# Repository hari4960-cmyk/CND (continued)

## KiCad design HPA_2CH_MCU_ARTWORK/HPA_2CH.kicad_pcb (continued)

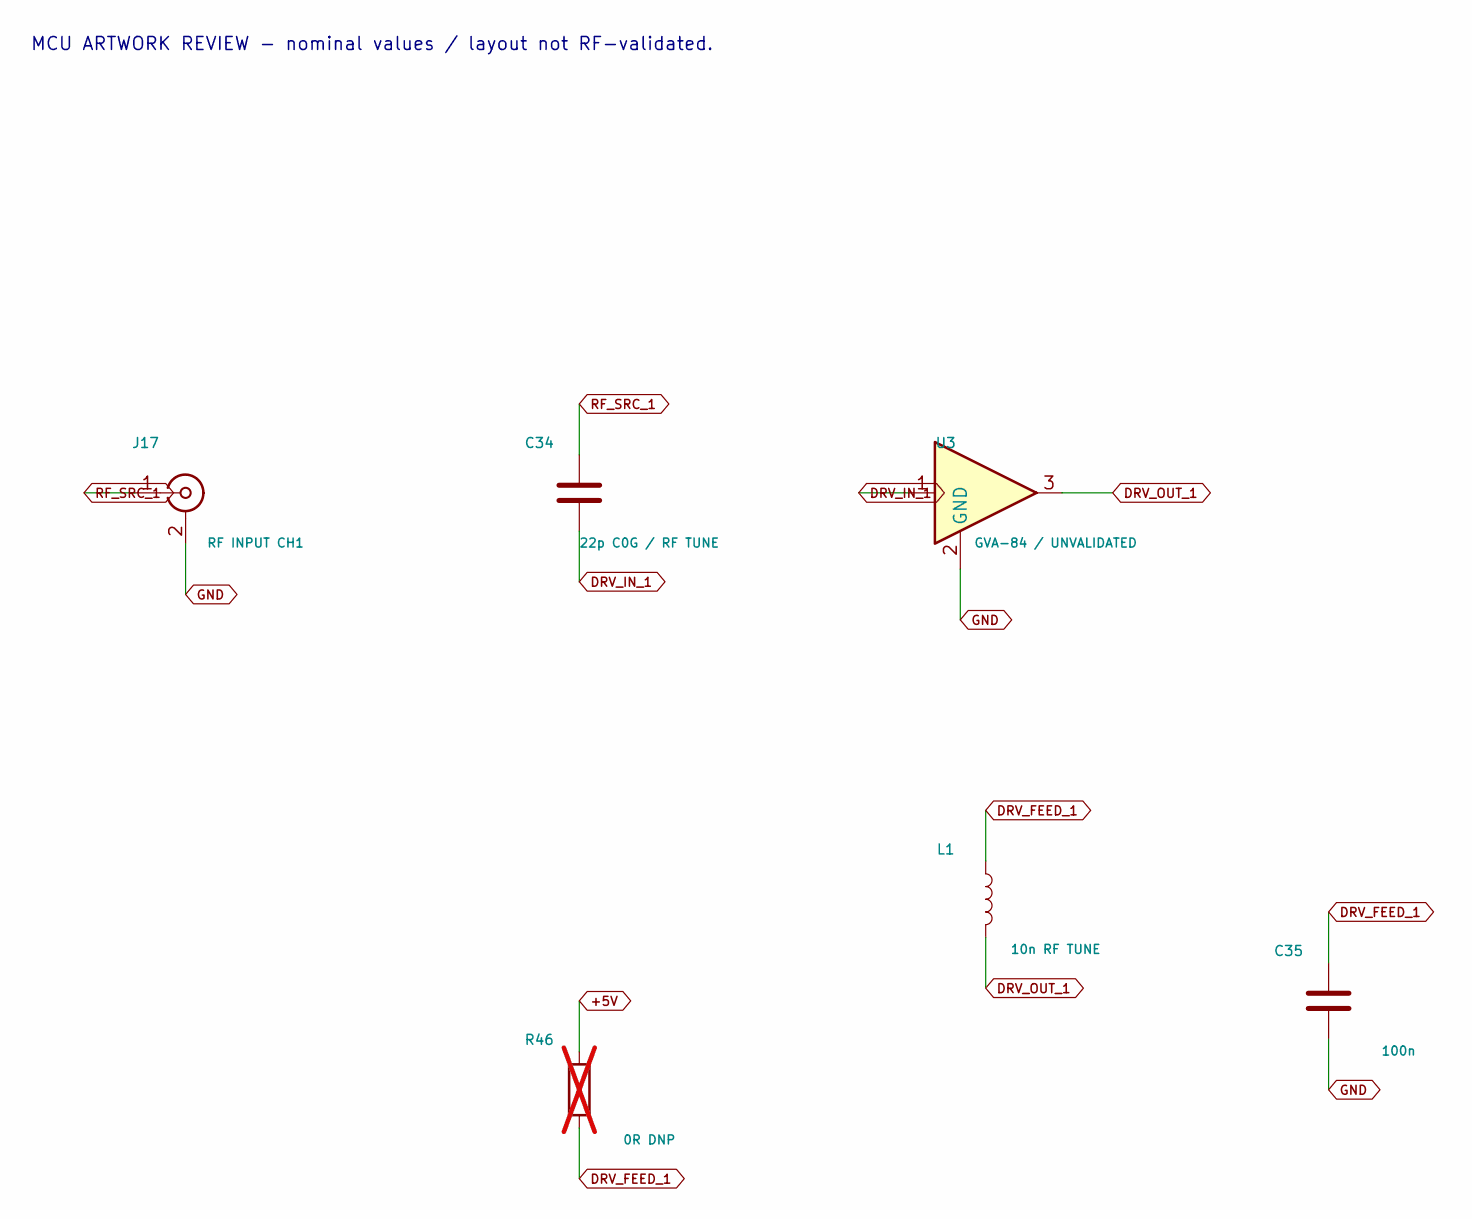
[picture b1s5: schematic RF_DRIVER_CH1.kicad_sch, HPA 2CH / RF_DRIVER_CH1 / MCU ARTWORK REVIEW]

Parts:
C34: 22p C0G / RF TUNE; C_0603_1608Metric
C35: 100n; C_0603_1608Metric
J17: RF INPUT CH1; SMA_Amphenol_132134_Vertical
L1: 10n RF TUNE; L_0805_2012Metric
R46: 0R DNP; R_0603_1608Metric; not fitted
U3: GVA-84 / UNVALIDATED; SOT-89-3

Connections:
+5V: R46.1; also elsewhere on the board
DRV_FEED_1: C35.1, L1.1, R46.2
DRV_IN_1: C34.2, U3.1
DRV_OUT_1: L1.2, U3.3; also elsewhere on the board
GND: C35.2, J17.2 (Ext), U3.2 (GND); also elsewhere on the board
RF_SRC_1: C34.1, J17.1 (In)

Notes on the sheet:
MCU ARTWORK REVIEW - nominal values / layout not RF-validated.

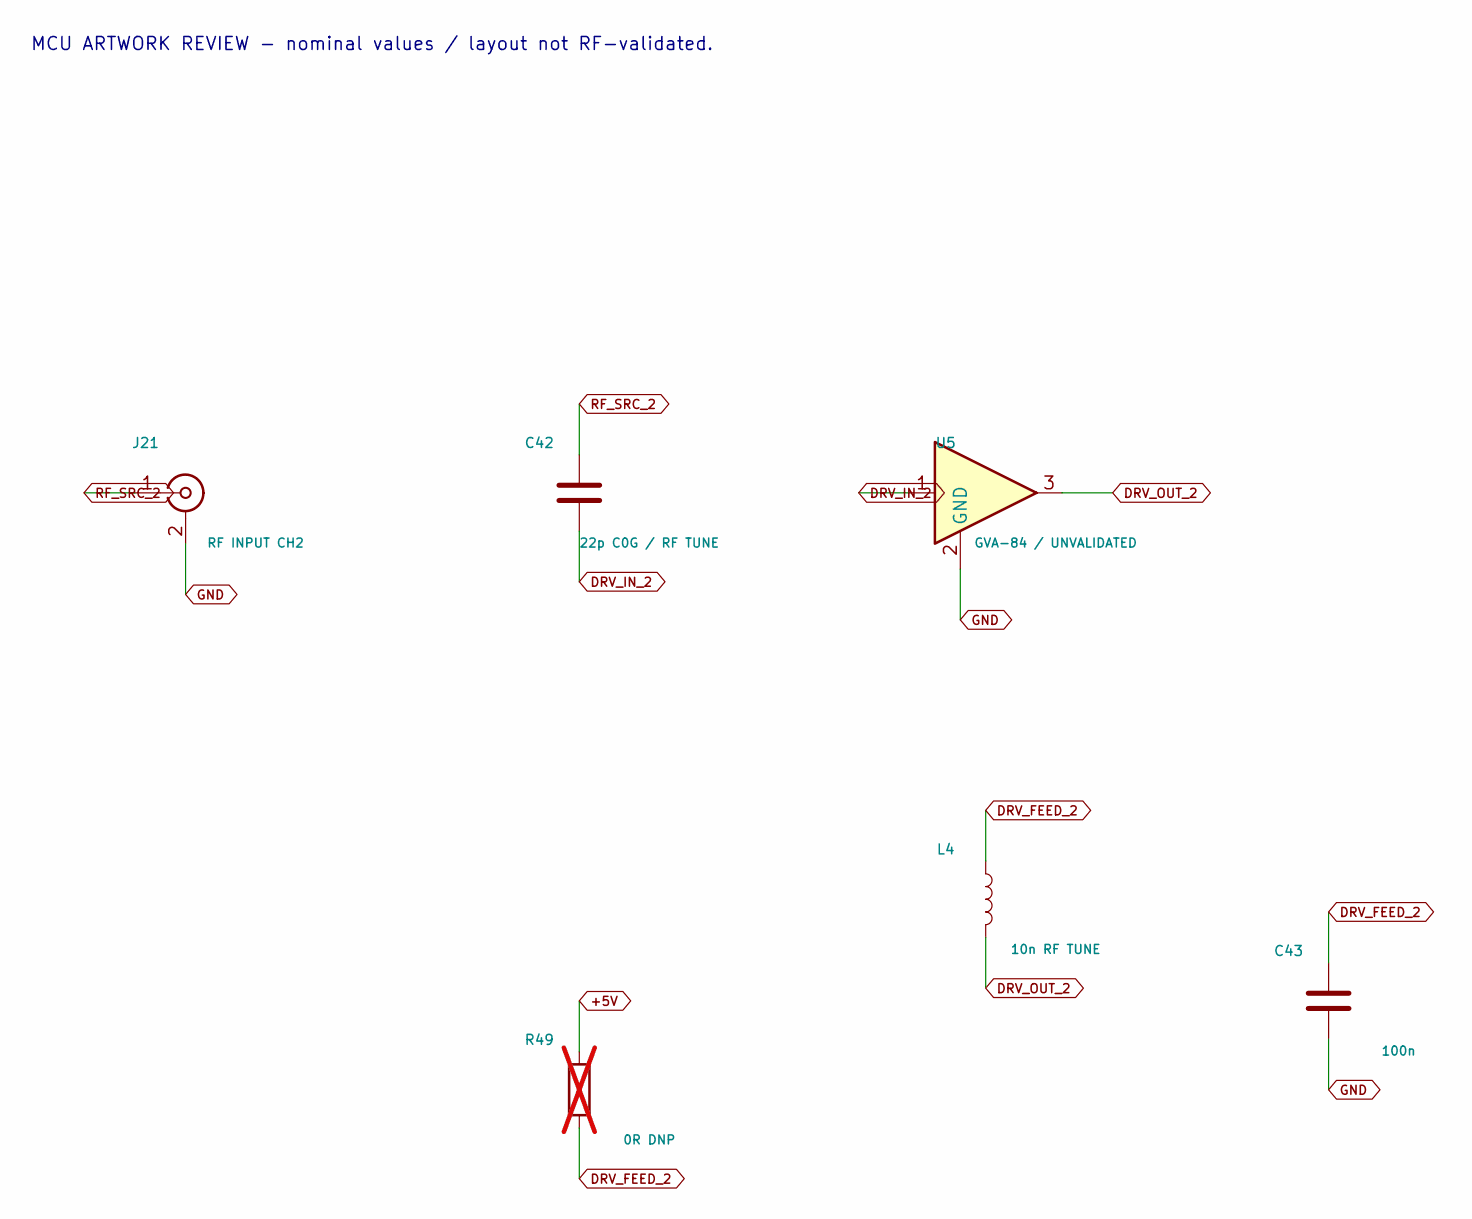
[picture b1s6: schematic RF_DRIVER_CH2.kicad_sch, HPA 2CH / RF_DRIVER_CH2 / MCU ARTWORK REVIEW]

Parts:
C42: 22p C0G / RF TUNE; C_0603_1608Metric
C43: 100n; C_0603_1608Metric
J21: RF INPUT CH2; SMA_Amphenol_132134_Vertical
L4: 10n RF TUNE; L_0805_2012Metric
R49: 0R DNP; R_0603_1608Metric; not fitted
U5: GVA-84 / UNVALIDATED; SOT-89-3

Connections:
+5V: R49.1; also elsewhere on the board
DRV_FEED_2: C43.1, L4.1, R49.2
DRV_IN_2: C42.2, U5.1
DRV_OUT_2: L4.2, U5.3; also elsewhere on the board
GND: C43.2, J21.2 (Ext), U5.2 (GND); also elsewhere on the board
RF_SRC_2: C42.1, J21.1 (In)

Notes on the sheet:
MCU ARTWORK REVIEW - nominal values / layout not RF-validated.

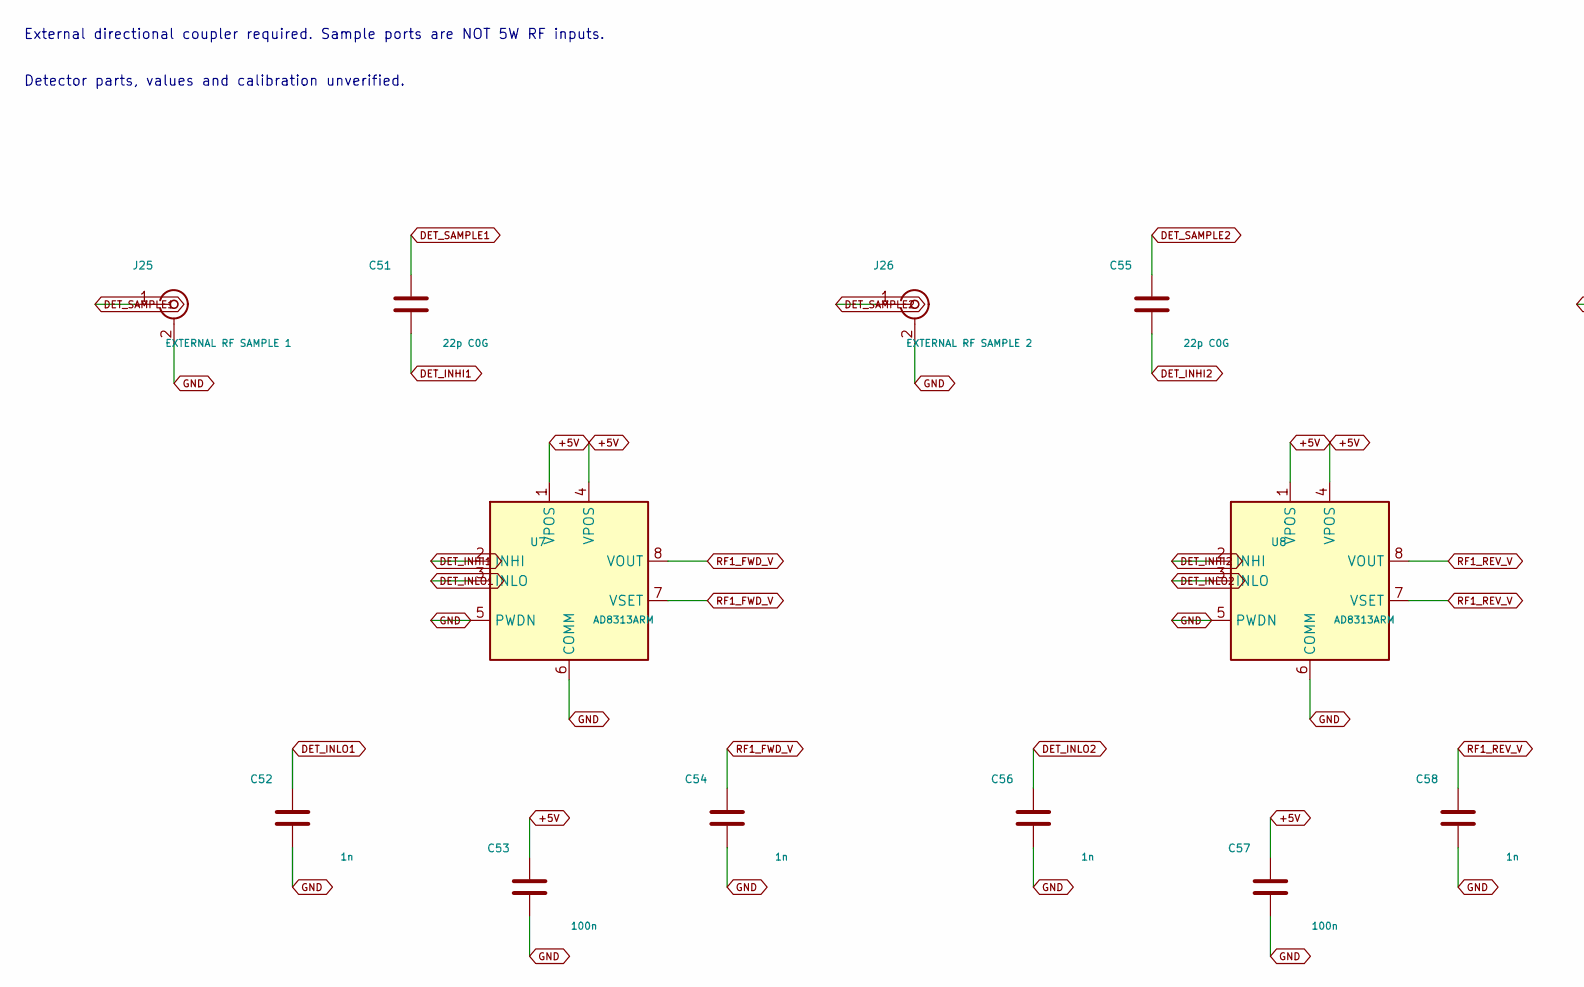
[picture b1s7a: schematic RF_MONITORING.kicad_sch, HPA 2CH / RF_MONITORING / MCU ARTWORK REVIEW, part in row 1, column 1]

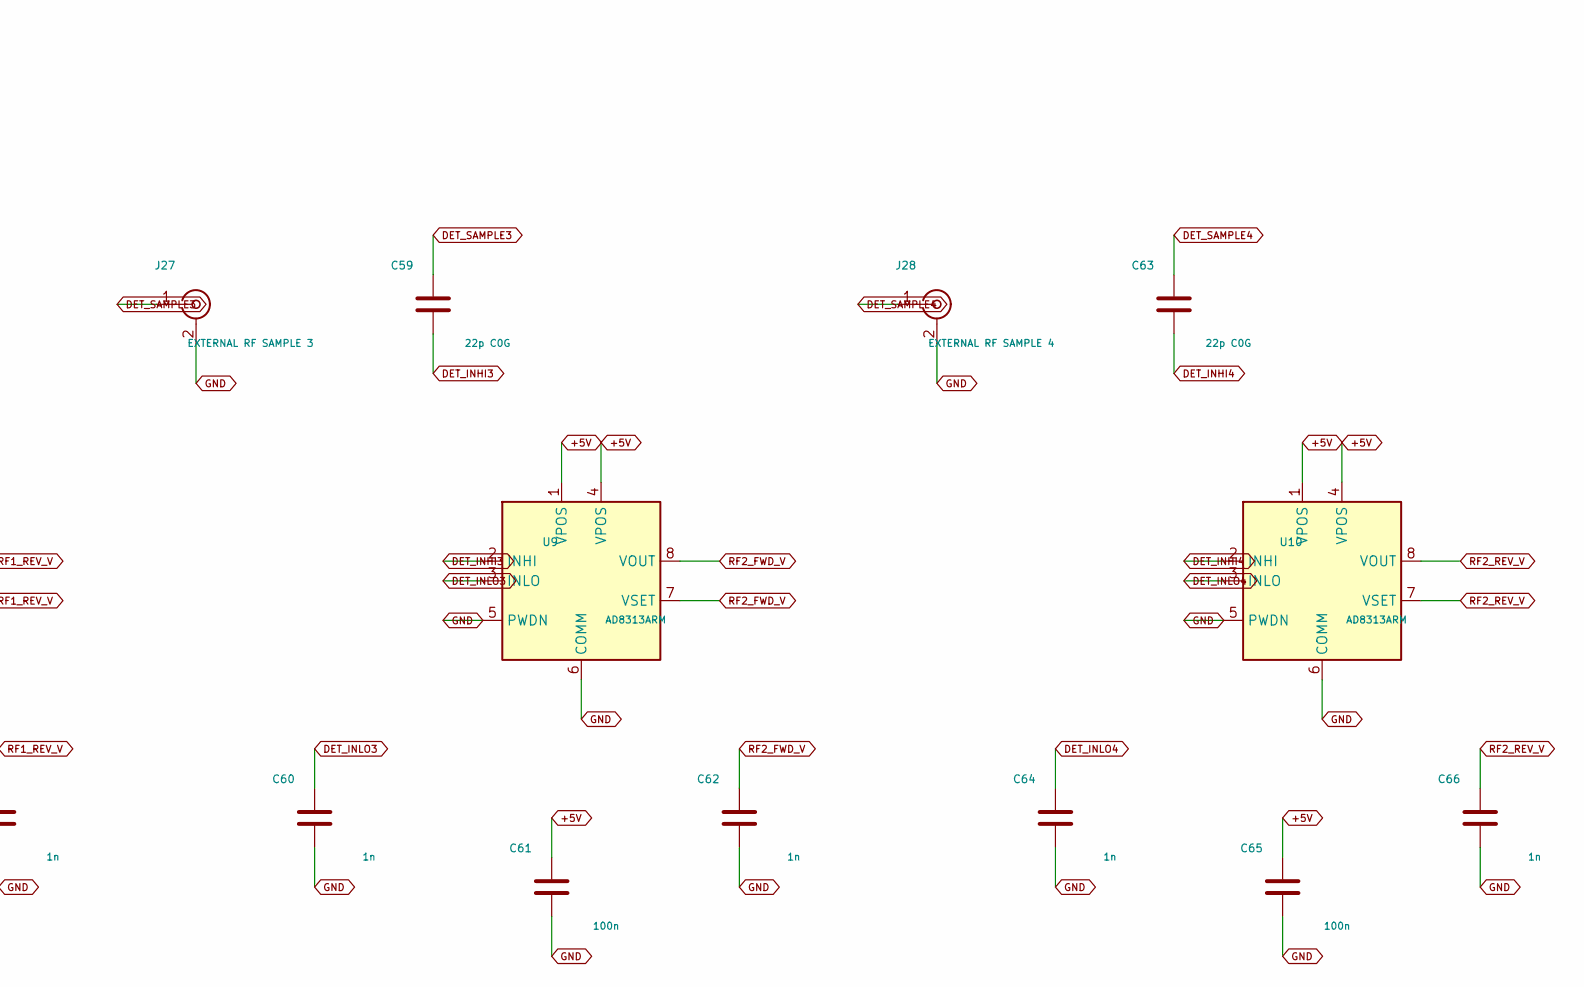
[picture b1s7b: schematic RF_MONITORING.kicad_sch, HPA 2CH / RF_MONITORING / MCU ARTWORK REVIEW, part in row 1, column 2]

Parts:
C51, C55, C59, C63: 22p C0G; C_0603_1608Metric
C52, C54, C56, C58, C60, C62, C64, C66: 1n; C_0603_1608Metric
C53, C57, C61, C65: 100n; C_0603_1608Metric
J25: EXTERNAL RF SAMPLE 1; SMA_Amphenol_132134_Vertical
J26: EXTERNAL RF SAMPLE 2; SMA_Amphenol_132134_Vertical
J27: EXTERNAL RF SAMPLE 3; SMA_Amphenol_132134_Vertical
J28: EXTERNAL RF SAMPLE 4; SMA_Amphenol_132134_Vertical
U7, U8, U9, U10: AD8313ARM; MSOP-8_3x3mm_P0.65mm

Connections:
+5V: C53.1, C57.1, C61.1, C65.1, U7.1 (VPOS), U7.4 (VPOS), U8.1 (VPOS), U8.4 (VPOS), U9.1 (VPOS), U9.4 (VPOS), U10.1 (VPOS), U10.4 (VPOS); also elsewhere on the board
DET_INHI1: C51.2, U7.2 (INHI)
DET_INHI2: C55.2, U8.2 (INHI)
DET_INHI3: C59.2, U9.2 (INHI)
DET_INHI4: C63.2, U10.2 (INHI)
DET_INLO1: C52.1, U7.3 (INLO)
DET_INLO2: C56.1, U8.3 (INLO)
DET_INLO3: C60.1, U9.3 (INLO)
DET_INLO4: C64.1, U10.3 (INLO)
DET_SAMPLE1: C51.1, J25.1 (In)
DET_SAMPLE2: C55.1, J26.1 (In)
DET_SAMPLE3: C59.1, J27.1 (In)
DET_SAMPLE4: C63.1, J28.1 (In)
GND: C52.2, C53.2, C54.2, C56.2, C57.2, C58.2, C60.2, C61.2, C62.2, C64.2, C65.2, C66.2, J25.2 (Ext), J26.2 (Ext), J27.2 (Ext), J28.2 (Ext), U7.5 (PWDN), U7.6 (COMM), U8.5 (PWDN), U8.6 (COMM), U9.5 (PWDN), U9.6 (COMM), U10.5 (PWDN), U10.6 (COMM); also elsewhere on the board
RF1_FWD_V: C54.1, U7.7 (VSET), U7.8 (VOUT); also elsewhere on the board
RF1_REV_V: C58.1, U8.7 (VSET), U8.8 (VOUT); also elsewhere on the board
RF2_FWD_V: C62.1, U9.7 (VSET), U9.8 (VOUT); also elsewhere on the board
RF2_REV_V: C66.1, U10.7 (VSET), U10.8 (VOUT); also elsewhere on the board

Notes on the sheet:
External directional coupler required. Sample ports are NOT 5W RF inputs.
Detector parts, values and calibration unverified.

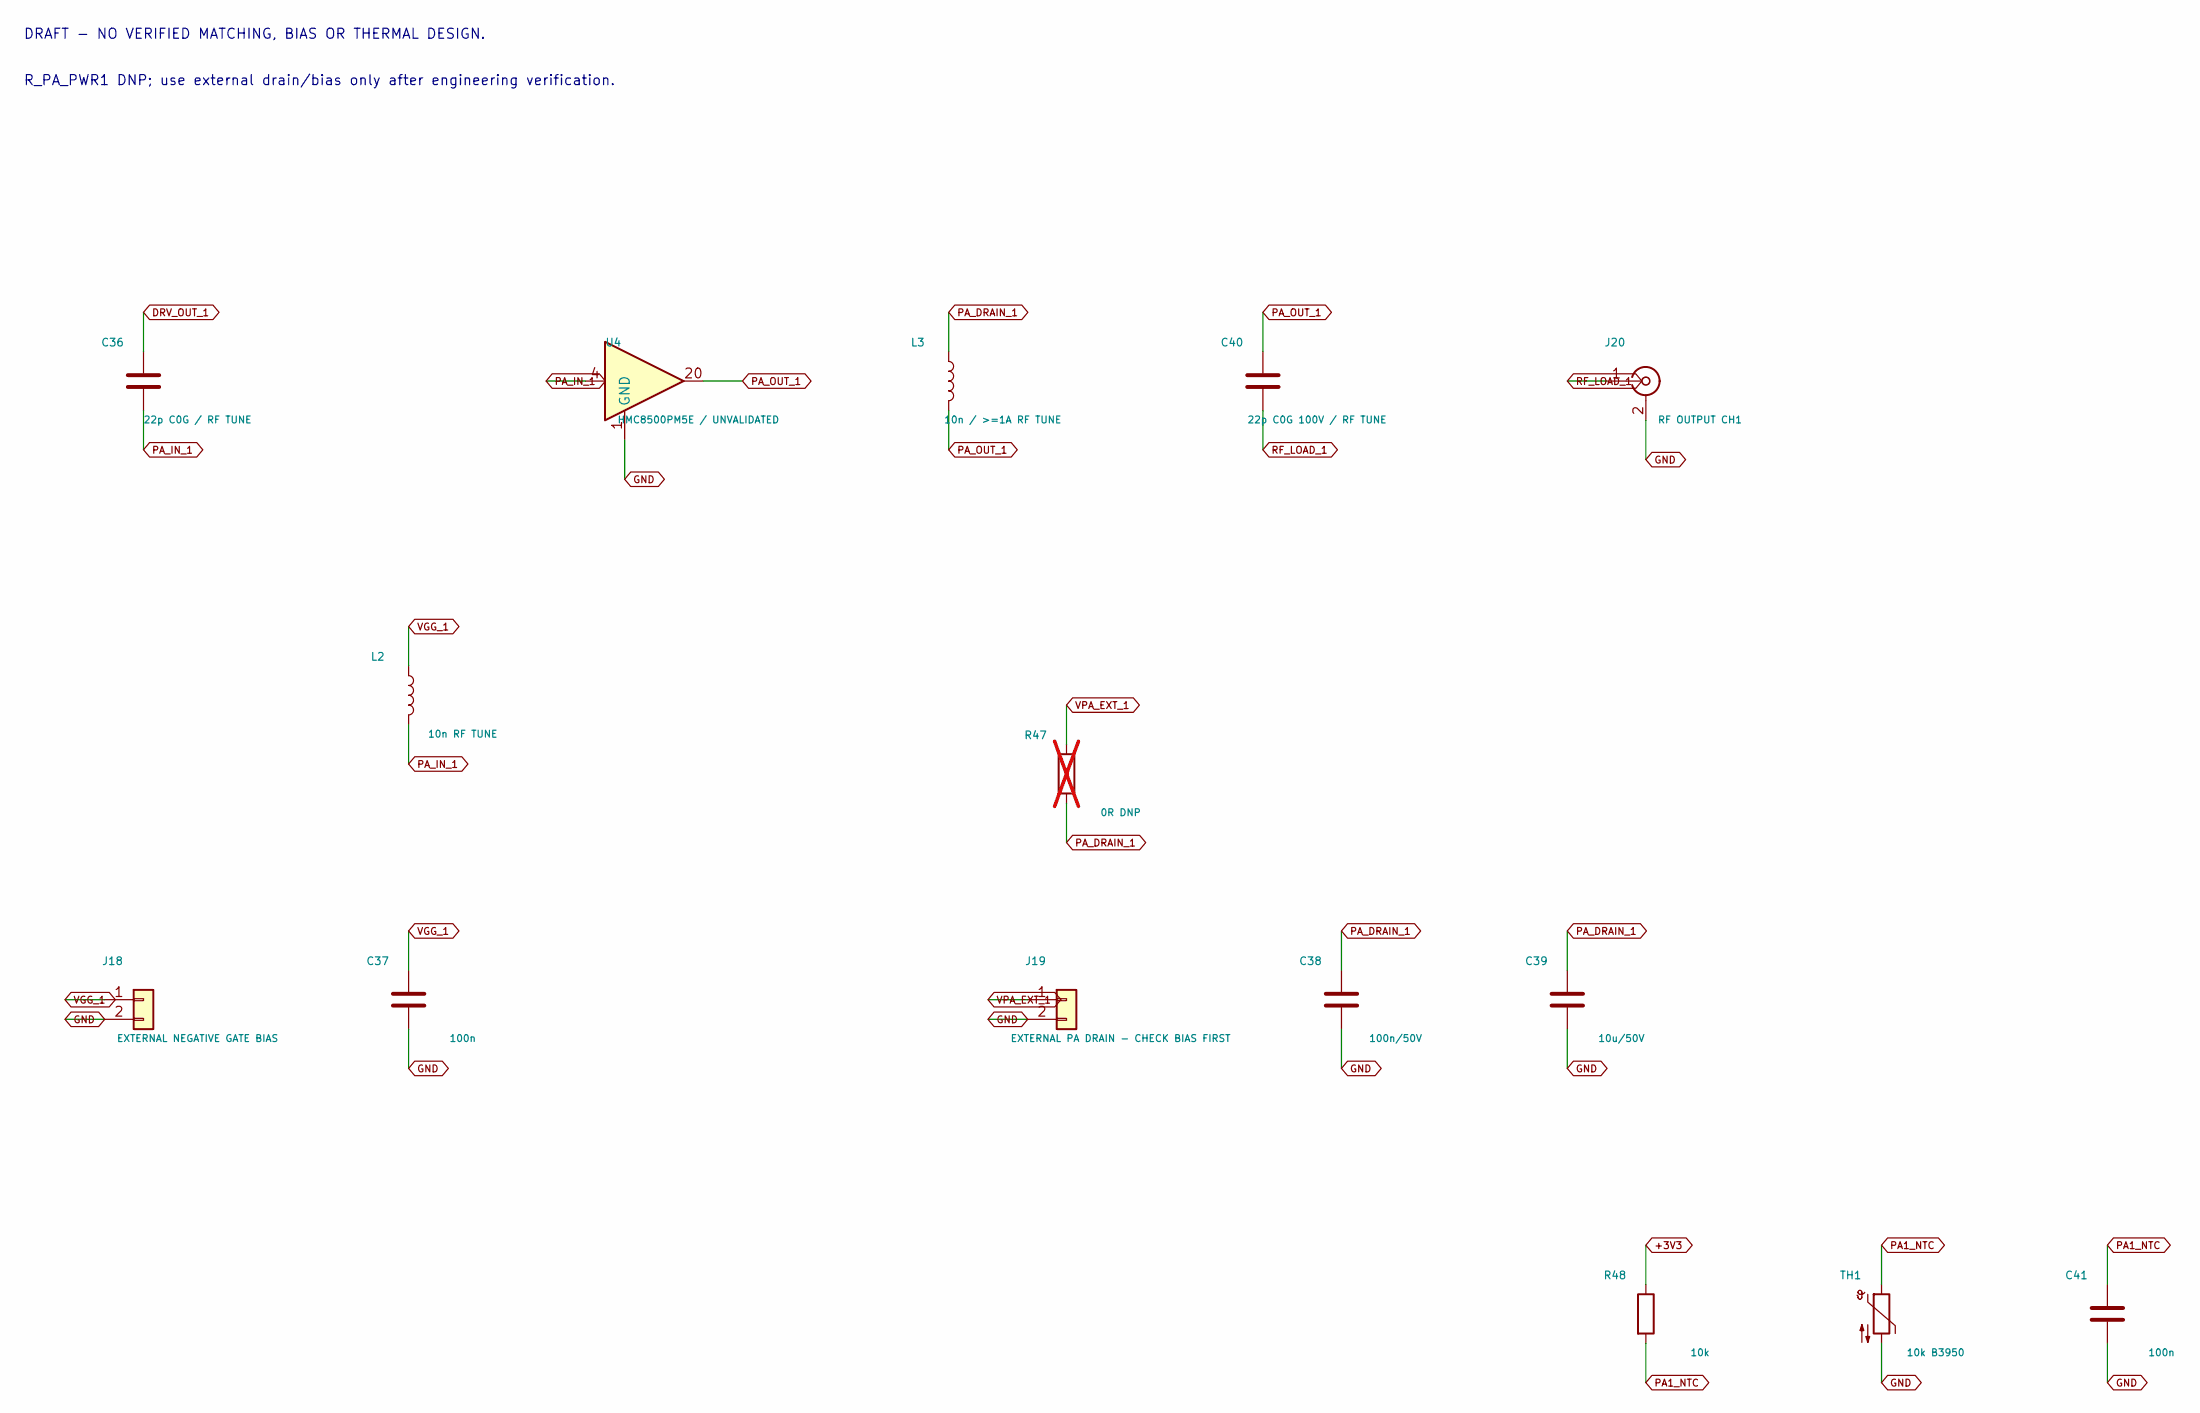
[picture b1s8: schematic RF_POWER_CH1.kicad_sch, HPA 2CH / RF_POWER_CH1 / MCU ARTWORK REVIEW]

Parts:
C36: 22p C0G / RF TUNE; C_0603_1608Metric
C37, C41: 100n; C_0603_1608Metric
C38: 100n/50V; C_0603_1608Metric
C39: 10u/50V; C_1210_3225Metric
C40: 22p C0G 100V / RF TUNE; C_0603_1608Metric
J18: EXTERNAL NEGATIVE GATE BIAS; PinHeader_1x02_P2.54mm_Vertical
J19: EXTERNAL PA DRAIN - CHECK BIAS FIRST; PinHeader_1x02_P2.54mm_Vertical
J20: RF OUTPUT CH1; SMA_Amphenol_132134_Vertical
L2: 10n RF TUNE; L_0805_2012Metric
L3: 10n / >=1A RF TUNE; L_0805_2012Metric
R47: 0R DNP; R_0603_1608Metric; not fitted
R48: 10k; R_0603_1608Metric
TH1: 10k B3950; R_0603_1608Metric
U4: HMC8500PM5E / UNVALIDATED; LFCSP-32-1EP_5x5mm_P0.5mm_EP3.1x3.1mm

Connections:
+3V3: R48.1; also elsewhere on the board
DRV_OUT_1: C36.1; also elsewhere on the board
GND: C37.2, C38.2, C39.2, C41.2, J18.2, J19.2, J20.2 (Ext), TH1.2, U4.1 (GND), U4.2 (GND), U4.3 (GND), U4.6 (GND), U4.7 (GND), U4.8 (GND), U4.9 (GND), U4.10 (GND), U4.11 (GND), U4.12 (GND), U4.13 (GND), U4.14 (GND), U4.15 (GND), U4.16 (GND), U4.17 (GND), U4.18 (GND), U4.19 (GND), U4.22 (GND), U4.23 (GND), U4.24 (GND), U4.25 (GND), U4.26 (GND), U4.27 (GND), U4.28 (GND), U4.29 (GND), U4.30 (GND), U4.31 (GND), U4.32 (GND), U4.33 (GND); also elsewhere on the board
PA1_NTC: C41.1, R48.2, TH1.1; also elsewhere on the board
PA_DRAIN_1: C38.1, C39.1, L3.1, R47.2
PA_IN_1: C36.2, L2.2, U4.4, U4.5
PA_OUT_1: C40.1, L3.2, U4.20, U4.21
RF_LOAD_1: C40.2, J20.1 (In)
VGG_1: C37.1, J18.1, L2.1
VPA_EXT_1: J19.1, R47.1; also elsewhere on the board

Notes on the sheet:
DRAFT - NO VERIFIED MATCHING, BIAS OR THERMAL DESIGN.
R_PA_PWR1 DNP; use external drain/bias only after engineering verification.

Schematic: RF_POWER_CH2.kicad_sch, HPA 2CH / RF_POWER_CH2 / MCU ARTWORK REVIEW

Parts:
C44: 22p C0G / RF TUNE; C_0603_1608Metric
C45, C49: 100n; C_0603_1608Metric
C46: 100n/50V; C_0603_1608Metric
C47: 10u/50V; C_1210_3225Metric
C48: 22p C0G 100V / RF TUNE; C_0603_1608Metric
J22: EXTERNAL NEGATIVE GATE BIAS; PinHeader_1x02_P2.54mm_Vertical
J23: EXTERNAL PA DRAIN - CHECK BIAS FIRST; PinHeader_1x02_P2.54mm_Vertical
J24: RF OUTPUT CH2; SMA_Amphenol_132134_Vertical
L5: 10n RF TUNE; L_0805_2012Metric
L6: 10n / >=1A RF TUNE; L_0805_2012Metric
R50: 0R DNP; R_0603_1608Metric; not fitted
R51: 10k; R_0603_1608Metric
TH2: 10k B3950; R_0603_1608Metric
U6: HMC8500PM5E / UNVALIDATED; LFCSP-32-1EP_5x5mm_P0.5mm_EP3.1x3.1mm

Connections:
+3V3: R51.1; also elsewhere on the board
DRV_OUT_2: C44.1; also elsewhere on the board
GND: C45.2, C46.2, C47.2, C49.2, J22.2, J23.2, J24.2 (Ext), TH2.2, U6.1 (GND), U6.2 (GND), U6.3 (GND), U6.6 (GND), U6.7 (GND), U6.8 (GND), U6.9 (GND), U6.10 (GND), U6.11 (GND), U6.12 (GND), U6.13 (GND), U6.14 (GND), U6.15 (GND), U6.16 (GND), U6.17 (GND), U6.18 (GND), U6.19 (GND), U6.22 (GND), U6.23 (GND), U6.24 (GND), U6.25 (GND), U6.26 (GND), U6.27 (GND), U6.28 (GND), U6.29 (GND), U6.30 (GND), U6.31 (GND), U6.32 (GND), U6.33 (GND); also elsewhere on the board
PA2_NTC: C49.1, R51.2, TH2.1; also elsewhere on the board
PA_DRAIN_2: C46.1, C47.1, L6.1, R50.2
PA_IN_2: C44.2, L5.2, U6.4, U6.5
PA_OUT_2: C48.1, L6.2, U6.20, U6.21
RF_LOAD_2: C48.2, J24.1 (In)
VGG_2: C45.1, J22.1, L5.1
VPA_EXT_2: J23.1, R50.1

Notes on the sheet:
DRAFT - NO VERIFIED MATCHING, BIAS OR THERMAL DESIGN.
R_PA_PWR2 DNP; use external drain/bias only after engineering verification.

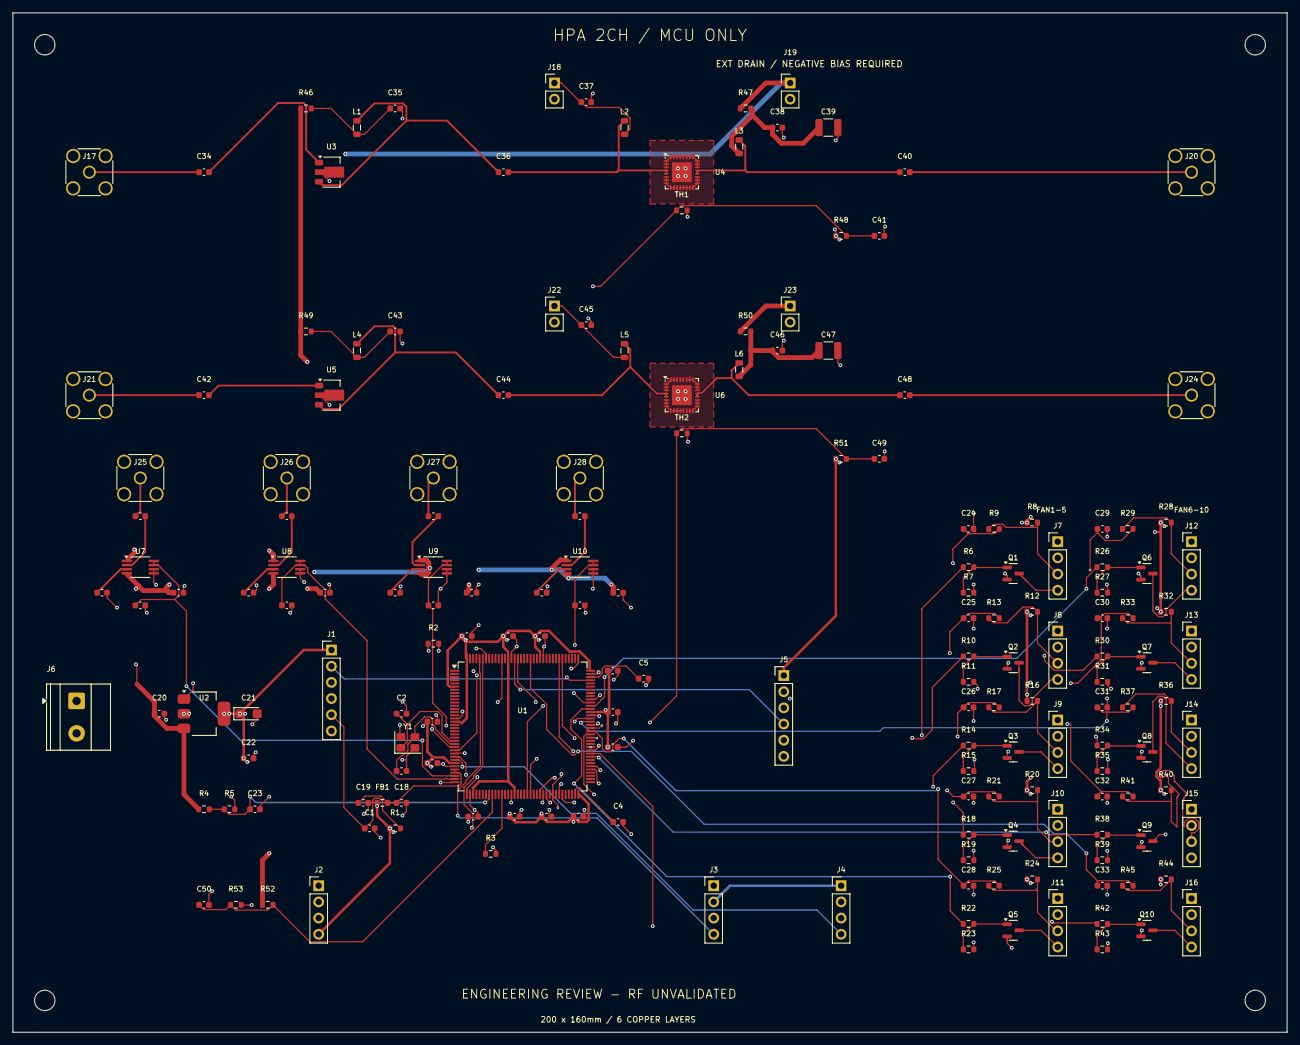
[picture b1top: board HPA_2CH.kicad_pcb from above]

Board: 6 copper layers, 200.0 x 160.0 mm, 181 parts (0 on the bottom side), 114 nets.

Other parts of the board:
H1, H2, H3, H4: MountingHole_3.2mm_M3

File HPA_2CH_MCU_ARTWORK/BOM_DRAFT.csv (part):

Reference,Function,Value,Footprint,DNP,Sheet
U1,U1,STM32F405ZGT6,Package_QFP:LQFP-144_20x20mm_P0.5mm,False,MAIN_CONTROLLER
J1,JSWD,SWD 3.3V + SWO,Connector_PinHeader_2.54mm:PinHeader_1x06_P2.54mm_Vertical,False,MAIN_CONTROLLER
J2,JUART,UART 3.3V,Connector_PinHeader_2.54mm:PinHeader_1x04_P2.54mm_Vertical,False,MAIN_CONTROLLER
J3,JI2C,I2C EXPANSION,Connector_PinHeader_2.54mm:PinHeader_1x04_P2.54mm_Vertical,False,MAIN_CONTROLLER
J4,JCURR,CURRENT 0..3.3V INPUTS,Connector_PinHeader_2.54mm:PinHeader_1x04_P2.54mm_Vertical,False,MAIN_CONTROLLER
J5,JRFCTRL,MCU RF CONTROL,Connector_PinHeader_2.54mm:PinHeader_1x06_P2.54mm_Vertical,False,MAIN_CONTROLLER
R1,R_RESET,10k,Resistor_SMD:R_0603_1608Metric,False,MAIN_CONTROLLER
C1,C_RESET,100n,Capacitor_SMD:C_0603_1608Metric,False,MAIN_CONTROLLER
R2,R_BOOT0,10k,Resistor_SMD:R_0603_1608Metric,False,MAIN_CONTROLLER
R3,R_BOOT1,10k,Resistor_SMD:R_0603_1608Metric,False,MAIN_CONTROLLER
Y1,Y1,8MHz / CL18pF,Crystal:Crystal_SMD_3225-4Pin_3.2x2.5mm,False,MAIN_CONTROLLER
C2,C_X1,33p C0G TUNE,Capacitor_SMD:C_0603_1608Metric,False,MAIN_CONTROLLER
C3,C_X2,33p C0G TUNE,Capacitor_SMD:C_0603_1608Metric,False,MAIN_CONTROLLER
C4,C_VCAP1,2.2u low ESR,Capacitor_SMD:C_0603_1608Metric,False,CORE_POWER
C5,C_VCAP2,2.2u low ESR,Capacitor_SMD:C_0603_1608Metric,False,CORE_POWER
C6,C_VDD17,100n,Capacitor_SMD:C_0603_1608Metric,False,CORE_POWER
C7,C_VDD30,100n,Capacitor_SMD:C_0603_1608Metric,False,CORE_POWER
C8,C_VDD39,100n,Capacitor_SMD:C_0603_1608Metric,False,CORE_POWER
C9,C_VDD52,100n,Capacitor_SMD:C_0603_1608Metric,False,CORE_POWER
C10,C_VDD62,100n,Capacitor_SMD:C_0603_1608Metric,False,CORE_POWER
C11,C_VDD72,100n,Capacitor_SMD:C_0603_1608Metric,False,CORE_POWER
C12,C_VDD84,100n,Capacitor_SMD:C_0603_1608Metric,False,CORE_POWER
C13,C_VDD95,100n,Capacitor_SMD:C_0603_1608Metric,False,CORE_POWER
C14,C_VDD108,100n,Capacitor_SMD:C_0603_1608Metric,False,CORE_POWER
C15,C_VDD121,100n,Capacitor_SMD:C_0603_1608Metric,False,CORE_POWER
C16,C_VDD131,100n,Capacitor_SMD:C_0603_1608Metric,False,CORE_POWER
C17,C_VDD144,100n,Capacitor_SMD:C_0603_1608Metric,False,CORE_POWER
FB1,FB1,600R@100MHz - VERIFY,Resistor_SMD:R_0603_1608Metric,False,CORE_POWER
C18,C_ADDA,100n,Capacitor_SMD:C_0603_1608Metric,False,CORE_POWER
C19,C_ADDB,1u,Capacitor_SMD:C_0603_1608Metric,False,CORE_POWER
J6,JPWR,+5V CONTROL/FANS,"TerminalBlock_Phoenix:TerminalBlock_Phoenix_MKDS-1,5-2-5.08_1x02_P5.08mm_Horizontal",False,CORE_POWER
U2,UREG,AMS1117-3.3,Package_TO_SOT_SMD:SOT-223-3_TabPin2,False,CORE_POWER
C20,C_IN,10u/10V,Capacitor_SMD:C_0603_1608Metric,False,CORE_POWER
C21,C_OUT,10u TANT / ESR VERIFY,Capacitor_Tantalum_SMD:CP_EIA-3216-18_Kemet-A,False,CORE_POWER
C22,C_BULK,4.7u,Capacitor_SMD:C_0603_1608Metric,False,CORE_POWER
R4,R_VIN_H,100k,Resistor_SMD:R_0603_1608Metric,False,CORE_POWER
R5,R_VIN_L,47k,Resistor_SMD:R_0603_1608Metric,False,CORE_POWER
C23,C_VINMON,100n,Capacitor_SMD:C_0603_1608Metric,False,CORE_POWER
J7,JF1,FAN1 5V 4WIRE,Connector_PinHeader_2.54mm:PinHeader_1x04_P2.54mm_Vertical,False,FAN_CONTROL
Q1,QF1,2N7002,Package_TO_SOT_SMD:SOT-23,False,FAN_CONTROL
R6,RG1,100,Resistor_SMD:R_0603_1608Metric,False,FAN_CONTROL
R7,RPD1,100k,Resistor_SMD:R_0603_1608Metric,False,FAN_CONTROL
R8,RTP1,10k,Resistor_SMD:R_0603_1608Metric,False,FAN_CONTROL
R9,RTS1,1k,Resistor_SMD:R_0603_1608Metric,False,FAN_CONTROL
C24,CT1,1n,Capacitor_SMD:C_0603_1608Metric,False,FAN_CONTROL
J8,JF2,FAN2 5V 4WIRE,Connector_PinHeader_2.54mm:PinHeader_1x04_P2.54mm_Vertical,False,FAN_CONTROL
Q2,QF2,2N7002,Package_TO_SOT_SMD:SOT-23,False,FAN_CONTROL
R10,RG2,100,Resistor_SMD:R_0603_1608Metric,False,FAN_CONTROL
R11,RPD2,100k,Resistor_SMD:R_0603_1608Metric,False,FAN_CONTROL
R12,RTP2,10k,Resistor_SMD:R_0603_1608Metric,False,FAN_CONTROL
R13,RTS2,1k,Resistor_SMD:R_0603_1608Metric,False,FAN_CONTROL
C25,CT2,1n,Capacitor_SMD:C_0603_1608Metric,False,FAN_CONTROL
J9,JF3,FAN3 5V 4WIRE,Connector_PinHeader_2.54mm:PinHeader_1x04_P2.54mm_Vertical,False,FAN_CONTROL
Q3,QF3,2N7002,Package_TO_SOT_SMD:SOT-23,False,FAN_CONTROL
R14,RG3,100,Resistor_SMD:R_0603_1608Metric,False,FAN_CONTROL
R15,RPD3,100k,Resistor_SMD:R_0603_1608Metric,False,FAN_CONTROL
R16,RTP3,10k,Resistor_SMD:R_0603_1608Metric,False,FAN_CONTROL
R17,RTS3,1k,Resistor_SMD:R_0603_1608Metric,False,FAN_CONTROL
C26,CT3,1n,Capacitor_SMD:C_0603_1608Metric,False,FAN_CONTROL
J10,JF4,FAN4 5V 4WIRE,Connector_PinHeader_2.54mm:PinHeader_1x04_P2.54mm_Vertical,False,FAN_CONTROL
Q4,QF4,2N7002,Package_TO_SOT_SMD:SOT-23,False,FAN_CONTROL
R18,RG4,100,Resistor_SMD:R_0603_1608Metric,False,FAN_CONTROL
R19,RPD4,100k,Resistor_SMD:R_0603_1608Metric,False,FAN_CONTROL
R20,RTP4,10k,Resistor_SMD:R_0603_1608Metric,False,FAN_CONTROL
R21,RTS4,1k,Resistor_SMD:R_0603_1608Metric,False,FAN_CONTROL
C27,CT4,1n,Capacitor_SMD:C_0603_1608Metric,False,FAN_CONTROL
J11,JF5,FAN5 5V 4WIRE,Connector_PinHeader_2.54mm:PinHeader_1x04_P2.54mm_Vertical,False,FAN_CONTROL
Q5,QF5,2N7002,Package_TO_SOT_SMD:SOT-23,False,FAN_CONTROL
R22,RG5,100,Resistor_SMD:R_0603_1608Metric,False,FAN_CONTROL
R23,RPD5,100k,Resistor_SMD:R_0603_1608Metric,False,FAN_CONTROL
R24,RTP5,10k,Resistor_SMD:R_0603_1608Metric,False,FAN_CONTROL
R25,RTS5,1k,Resistor_SMD:R_0603_1608Metric,False,FAN_CONTROL
C28,CT5,1n,Capacitor_SMD:C_0603_1608Metric,False,FAN_CONTROL
J12,JF6,FAN6 5V 4WIRE,Connector_PinHeader_2.54mm:PinHeader_1x04_P2.54mm_Vertical,False,FAN_CONTROL
Q6,QF6,2N7002,Package_TO_SOT_SMD:SOT-23,False,FAN_CONTROL
R26,RG6,100,Resistor_SMD:R_0603_1608Metric,False,FAN_CONTROL
R27,RPD6,100k,Resistor_SMD:R_0603_1608Metric,False,FAN_CONTROL
R28,RTP6,10k,Resistor_SMD:R_0603_1608Metric,False,FAN_CONTROL
R29,RTS6,1k,Resistor_SMD:R_0603_1608Metric,False,FAN_CONTROL
C29,CT6,1n,Capacitor_SMD:C_0603_1608Metric,False,FAN_CONTROL
J13,JF7,FAN7 5V 4WIRE,Connector_PinHeader_2.54mm:PinHeader_1x04_P2.54mm_Vertical,False,FAN_CONTROL
Q7,QF7,2N7002,Package_TO_SOT_SMD:SOT-23,False,FAN_CONTROL
R30,RG7,100,Resistor_SMD:R_0603_1608Metric,False,FAN_CONTROL
R31,RPD7,100k,Resistor_SMD:R_0603_1608Metric,False,FAN_CONTROL
R32,RTP7,10k,Resistor_SMD:R_0603_1608Metric,False,FAN_CONTROL
R33,RTS7,1k,Resistor_SMD:R_0603_1608Metric,False,FAN_CONTROL
C30,CT7,1n,Capacitor_SMD:C_0603_1608Metric,False,FAN_CONTROL
J14,JF8,FAN8 5V 4WIRE,Connector_PinHeader_2.54mm:PinHeader_1x04_P2.54mm_Vertical,False,FAN_CONTROL
Q8,QF8,2N7002,Package_TO_SOT_SMD:SOT-23,False,FAN_CONTROL
R34,RG8,100,Resistor_SMD:R_0603_1608Metric,False,FAN_CONTROL
R35,RPD8,100k,Resistor_SMD:R_0603_1608Metric,False,FAN_CONTROL
R36,RTP8,10k,Resistor_SMD:R_0603_1608Metric,False,FAN_CONTROL
R37,RTS8,1k,Resistor_SMD:R_0603_1608Metric,False,FAN_CONTROL
C31,CT8,1n,Capacitor_SMD:C_0603_1608Metric,False,FAN_CONTROL
J15,JF9,FAN9 5V 4WIRE,Connector_PinHeader_2.54mm:PinHeader_1x04_P2.54mm_Vertical,False,FAN_CONTROL
Q9,QF9,2N7002,Package_TO_SOT_SMD:SOT-23,False,FAN_CONTROL
R38,RG9,100,Resistor_SMD:R_0603_1608Metric,False,FAN_CONTROL
R39,RPD9,100k,Resistor_SMD:R_0603_1608Metric,False,FAN_CONTROL
R40,RTP9,10k,Resistor_SMD:R_0603_1608Metric,False,FAN_CONTROL
R41,RTS9,1k,Resistor_SMD:R_0603_1608Metric,False,FAN_CONTROL
C32,CT9,1n,Capacitor_SMD:C_0603_1608Metric,False,FAN_CONTROL
J16,JF10,FAN10 5V 4WIRE,Connector_PinHeader_2.54mm:PinHeader_1x04_P2.54mm_Vertical,False,FAN_CONTROL
Q10,QF10,2N7002,Package_TO_SOT_SMD:SOT-23,False,FAN_CONTROL
R42,RG10,100,Resistor_SMD:R_0603_1608Metric,False,FAN_CONTROL
R43,RPD10,100k,Resistor_SMD:R_0603_1608Metric,False,FAN_CONTROL
R44,RTP10,10k,Resistor_SMD:R_0603_1608Metric,False,FAN_CONTROL
R45,RTS10,1k,Resistor_SMD:R_0603_1608Metric,False,FAN_CONTROL
C33,CT10,1n,Capacitor_SMD:C_0603_1608Metric,False,FAN_CONTROL
J17,JRF_IN1,RF INPUT CH1,Connector_Coaxial:SMA_Amphenol_132134_Vertical,False,RF_DRIVER_CH1
C34,C_RFIN1,22p C0G / RF TUNE,Capacitor_SMD:C_0603_1608Metric,False,RF_DRIVER_CH1
U3,UDRV1,GVA-84 / UNVALIDATED,Package_TO_SOT_SMD:SOT-89-3,False,RF_DRIVER_CH1
L1,LDRV1,10n RF TUNE,Inductor_SMD:L_0805_2012Metric,False,RF_DRIVER_CH1
R46,R_DRV_PWR1,0R DNP,Resistor_SMD:R_0603_1608Metric,True,RF_DRIVER_CH1
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
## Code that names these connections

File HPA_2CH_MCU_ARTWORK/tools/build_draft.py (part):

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 if nm in ['VDDA','VREF+']:mp[num]='VDDA'
 if nm.startswith('VCAP'):mp[num]=nm
for n in ['NRST','BOOT0']:mp[pm[n]]=n
for n in ['PH0','PH1']:mp[pm[n]]='HSE_IN' if n=='PH0' else 'HSE_OUT'
mp[pm['PB2']]='BOOT1'
for i,g in enumerate(['PE9','PE11','PE13','PE14','PC6','PC7','PC8','PC9','PD12','PD13'],1):mp[pm[g]]=f'FAN_PWM_{i}'
for i in range(10):mp[pm[f'PG{i}']]=f'FAN_TACH_{i+1}'
for g,n in [('PG13','PA1_ENABLE_CMD'),('PG14','PA2_ENABLE_CMD'),('PD0','RF1_FAULT'),('PD1','RF2_FAULT'),('PD8','UART_TX'),('PD9','UART_RX'),('PB8','I2C_SCL'),('PB9','I2C_SDA'),('PA13','SWDIO'),('PA14','SWCLK'),('PB3','SWO')]:mp[pm[g]]=n
for i,n in enumerate(['RF1_FWD_V','RF1_REV_V','RF2_FWD_V','RF2_REV_V']):mp[pm[f'PA{i}']]=n
for i,n in enumerate(['PA1_NTC','PA2_NTC','PA1_I_MON','PA2_I_MON','VIN_MON','VPA_MON']):mp[pm[f'PC{i}']]=n
add('MAIN_CONTROLLER','U1','MCU_ST_STM32F4','STM32F405ZGTx','STM32F405ZGT6','Package_QFP:LQFP-144_20x20mm_P0.5mm',mp,(85,145),(80,112))
conn('MAIN_CONTROLLER','JSWD',6,'SWD 3.3V + SWO',{1:'+3V3',2:'SWDIO',3:'GND',4:'SWCLK',5:'NRST',6:'SWO'},(180,50),(52,92))
conn('MAIN_CONTROLLER','JUART',4,'UART 3.3V',{1:'GND',2:'UART_TX',3:'UART_RX',4:'+3V3'},(180,85),(48,137))
conn('MAIN_CONTROLLER','JI2C',4,'I2C EXPANSION',{1:'GND',2:'+3V3',3:'I2C_SCL',4:'I2C_SDA'},(180,120),(110,137))
conn('MAIN_CONTROLLER','JCURR',4,'CURRENT 0..3.3V INPUTS',{1:'+3V3',2:'GND',3:'PA1_I_MON',4:'PA2_I_MON'},(180,155),(130,137))
conn('MAIN_CONTROLLER','JRFCTRL',6,'MCU RF CONTROL',{1:'+3V3',2:'GND',3:'PA1_ENABLE_CMD',4:'PA2_ENABLE_CMD',5:'RF1_FAULT',6:'RF2_FAULT'},(180,210),(121,104))
resistor('MAIN_CONTROLLER','R_RESET','10k','+3V3','NRST',(260,45),(60,128));cap('MAIN_CONTROLLER','C_RESET','100n','NRST','GND',(280,45),(56,128))
resistor('MAIN_CONTROLLER','R_BOOT0','10k','BOOT0','GND',(260,80),(67,94));resistor('MAIN_CONTROLLER','R_BOOT1','10k','BOOT1','GND',(280,80),(75,132))
add('MAIN_CONTROLLER','Y1','Device','Crystal_GND24','8MHz / CL18pF','Crystal:Crystal_SMD_3225-4Pin_3.2x2.5mm',{1:'HSE_IN',3:'HSE_OUT',2:'GND',4:'GND'},(260,120),(62,114.5))
cap('MAIN_CONTROLLER','C_X1','33p C0G TUNE','HSE_IN','GND',(250,145),(61,110));cap('MAIN_CONTROLLER','C_X2','33p C0G TUNE','HSE_OUT','GND',(275,145),(61,119))
cap('CORE_POWER','C_VCAP1','2.2u low ESR','VCAP_1','GND',(280,150),(95,127));cap('CORE_POWER','C_VCAP2','2.2u low ESR','VCAP_2','GND',(310,150),(99,104.5))
# Local decoupling positions derived from actual MCU footprint pad locations.
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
